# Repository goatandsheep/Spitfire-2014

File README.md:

McMaster Solar Car Club
=======================

Welcome to McMaster University's Solar Car Club's GitHub Repository. This is where we will keep all of our project files. We are currently in the process of transferring files from the Dropbox folder to here.

This is the link to the Solar Car Room Drawer Inventory: http://goo.gl/nMddYb

This is the link to the main Solar Car website: http://www.macsolarcar.com/

If you are new to GitHub, don't fret-we have included a tutorial on how to use it: http://goo.gl/4RcD2u

Note: [.md](https://en.wikipedia.org/wiki/Markdown) files can be opened like .txt files, but look cool up on GitHub

Target Release date: End of February, 2014

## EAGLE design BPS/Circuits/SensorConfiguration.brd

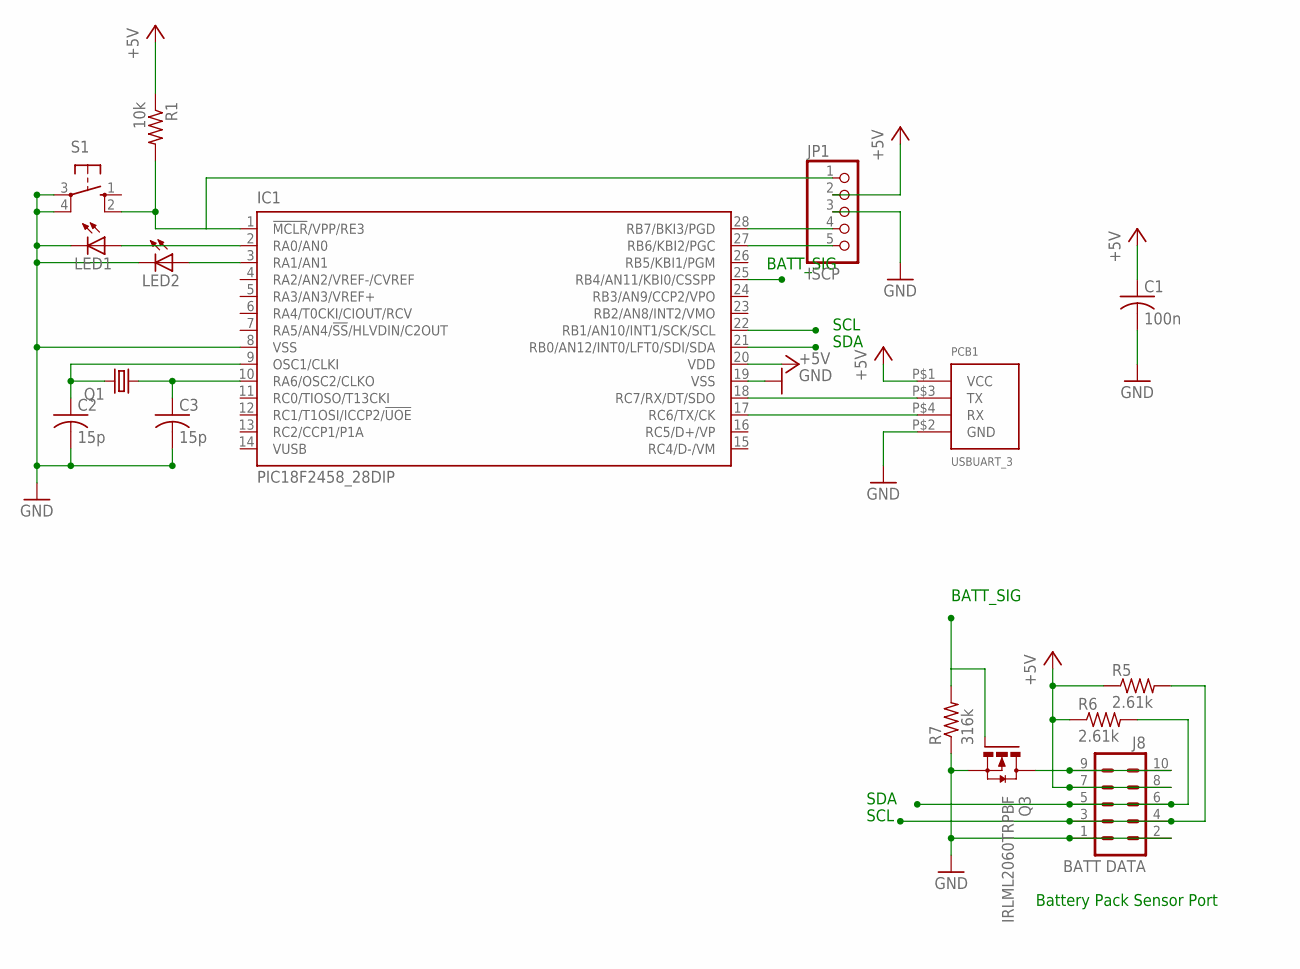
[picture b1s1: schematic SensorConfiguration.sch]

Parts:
C1: 100n; C0805
C2, C3: 15p; C0805
IC1: PIC18F2458_28DIP; DIL28-3
J8: BATT DATA; ML10
JP1: ISCP; 1X05
LED1, LED2: LED5MM
PCB1: USBUART_3; UB232R
Q1: CRYSTALHC49S; HC49/S
Q3: IRLML2060TRPBF; SOT23
R1: 10k; R0805
R5, R6: 2.61k; R0805
R7: 316k; R0805
S1: 10-XX; B3F-10XX

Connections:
+5V: C1.1, IC1.20 (VDD), J8.7, J8.8, JP1.2, PCB1.P$1 (VCC), R1.1, R5.1, R6.1
BSIG: IC1.25 (RB4/AN11/KBI0/CSSPP), Q3.1 (G), R7.2
GND: C1.2, C2.2, C3.2, IC1.8 (VSS), IC1.19 (VSS), J8.1, J8.2, JP1.3, LED1.K (C), LED2.K (C), PCB1.P$2 (GND), Q3.2 (S), R7.1, S1.3, S1.4 (P1)
unnamed: IC1.27 (RB6/KBI2/PGC), JP1.5
unnamed: IC1.18 (RC7/RX/DT/SDO), PCB1.P$3 (TX)
unnamed: IC1.17 (RC6/TX/CK), PCB1.P$4 (RX)
unnamed: IC1.28 (RB7/BKI3/PGD), JP1.4
unnamed: IC1.1 (!MCLR!/VPP/RE3), JP1.1, R1.2, S1.2 (S1)
unnamed: IC1.2 (RA0/AN0), LED1.A
unnamed: J8.9, J8.10, Q3.3 (D)
unnamed: IC1.3 (RA1/AN1), LED2.A
unnamed: C2.1, IC1.9 (OSC1/CLKI), Q1.2
unnamed: C3.1, IC1.10 (RA6/OSC2/CLKO), Q1.1
SCL: IC1.22 (RB1/AN10/INT1/SCK/SCL), J8.3, J8.4, R5.2
SDA: IC1.21 (RB0/AN12/INT0/LFT0/SDI/SDA), J8.5, J8.6, R6.2

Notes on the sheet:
SCL
SDA
Battery Pack Sensor Port
BATT_SIG

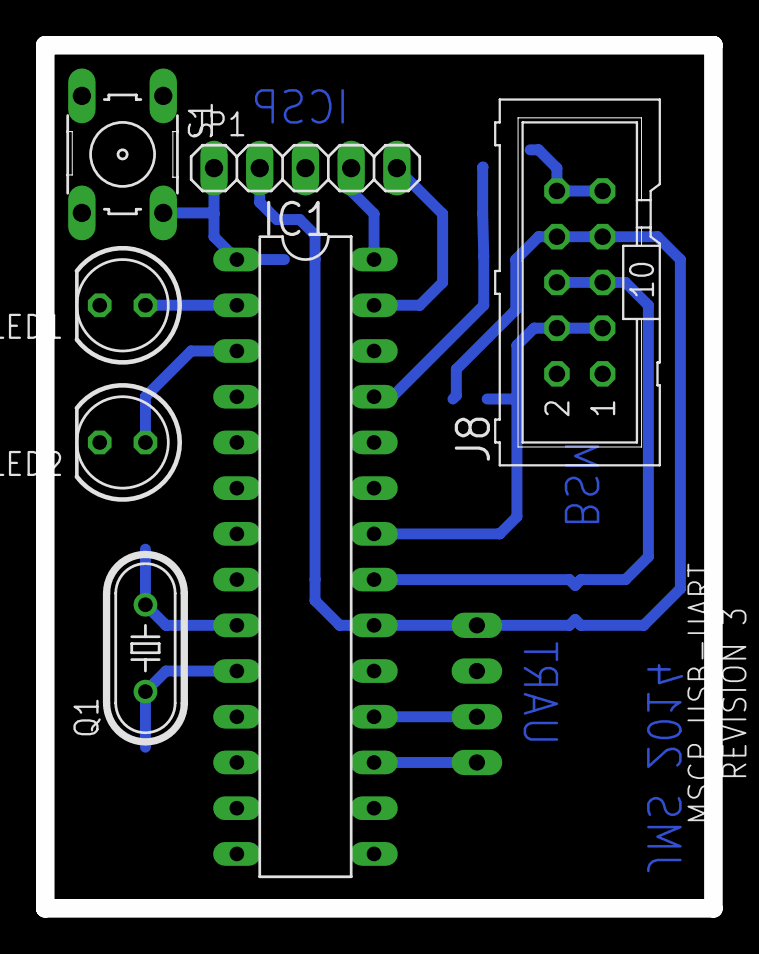
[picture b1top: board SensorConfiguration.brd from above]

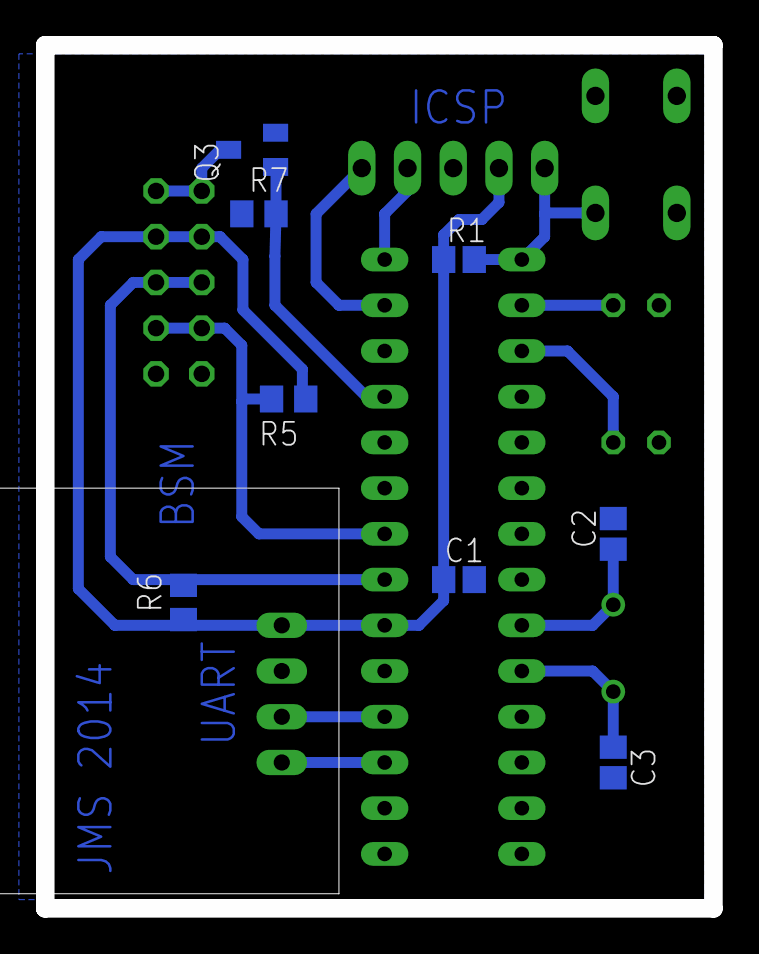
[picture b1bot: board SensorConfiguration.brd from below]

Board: 2 copper layers, 37.1 x 48.0 mm, 16 parts (8 on the bottom side), 15 nets.

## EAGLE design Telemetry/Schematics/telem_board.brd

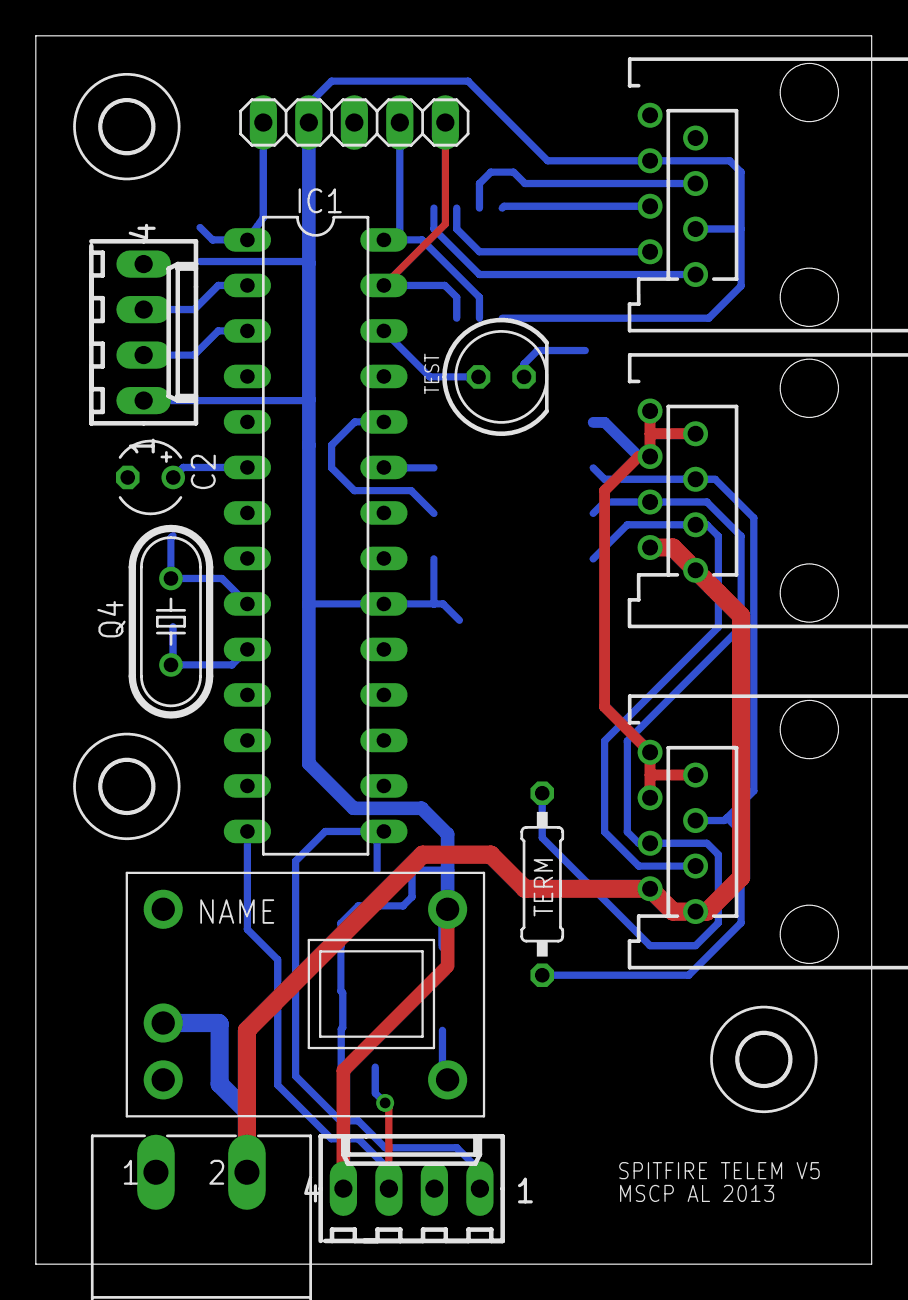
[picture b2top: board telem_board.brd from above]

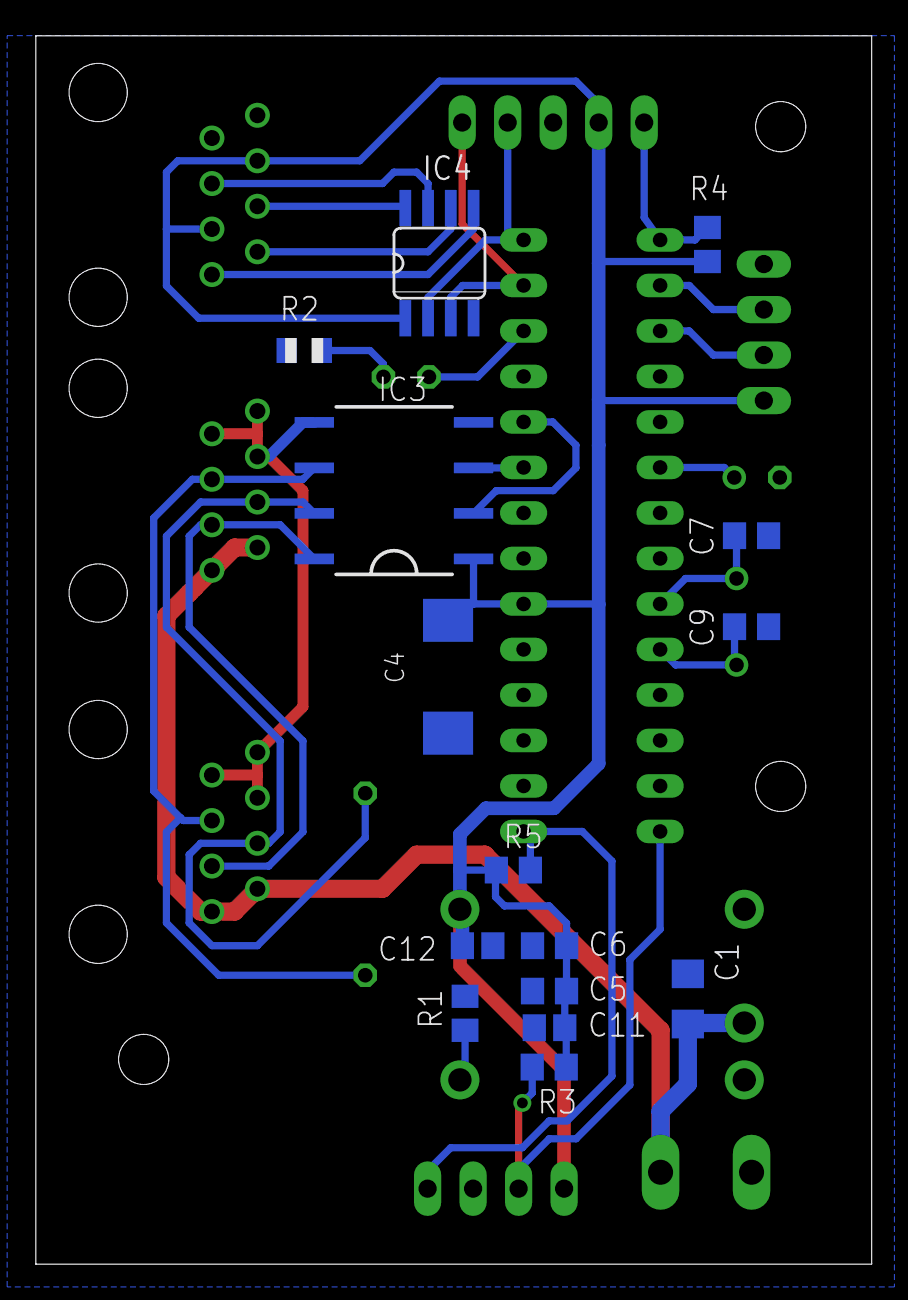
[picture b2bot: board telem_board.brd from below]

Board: 2 copper layers, 46.7 x 68.6 mm, 31 parts (15 on the bottom side), 26 nets.

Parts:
C1: 2.2u; C1206
C2: 10u; TT2D4
C4: 100u; SMC_D
C5: 1u; C0805
C6: 0.1u; C0805
C7, C9: 22p; C0805
C11: 10n; C0805
C12: 4.7u; C0805
H2, H3, H4: MOUNT-HOLE2.8; 2,8
IC1: PIC18F26K80I/SP; DIL28/3
IC2: PTN78000WAH; PTN78000
IC3: ISO1050DUB; DUB-R-PDSO-G8
IC4: SN75LBC179D; SO08
J1: ICD; 1X05
J2, J3: CANBUS; 215877-7
J4: HALLSENS; 6410-04
J5: TEMPSENS; 6410-04
J7: RADIO; 215877-7
Q4: 20M; HC49/S
R1: 21k; R0805
R2, R3, R5: R0805
R4: 10k; R0805
TERM: 100; 0207/10
TEST: LED5MM
X1: +12V; MSTBA2

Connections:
+5V: C4.+, C5.1, C6.2, C11.1, C12.1, IC1.20, IC2.P5, IC3.1, IC4.1, J1.2, J4.1, J5.4, J7.3, J7.6, R3.1, R4.2, R5.1
+12V: C1.1, IC2.P2, J2.1, J2.2, J3.1, J3.2, X1.2
CAN5V: IC3.8, J2.3, J3.3
CANGND: IC3.5, J2.6, J2.7, J2.8, J3.6, J3.7, J3.8
CANH: IC3.7, J2.4, J3.4, TERM.1
CANL: IC3.6, J2.5, J3.5, TERM.2
GND: C1.2, C2.-, C4.-, C5.2, C6.1, C7.2, C9.2, C11.2, C12.2, IC1.8, IC1.19, IC2.P1, IC3.4, IC4.4, J1.3, J4.4, J5.2, J7.7, J7.8, R1.1, R2.1, X1.1
unnamed: IC1.2, J4.3
unnamed: IC1.3, J4.2
unnamed: IC4.7, J7.5
unnamed: IC4.8, J7.4
unnamed: C2.+, IC1.6
unnamed: IC1.23, IC3.3
unnamed: R2.2, TEST.K
unnamed: IC2.P4, R1.2
unnamed: IC1.24, IC3.2
unnamed: IC4.6, J7.2
unnamed: IC1.26, TEST.A
unnamed: IC4.5, J7.1
unnamed: IC1.1, J1.1, R4.1
unnamed: C7.1, IC1.9, Q4.1
unnamed: C9.1, IC1.10, Q4.2
RX: IC1.28, IC4.2, J1.4
SCL: IC1.14, J5.3, R3.2
SDA: IC1.15, J5.1, R5.2
TX: IC1.27, IC4.3, J1.5

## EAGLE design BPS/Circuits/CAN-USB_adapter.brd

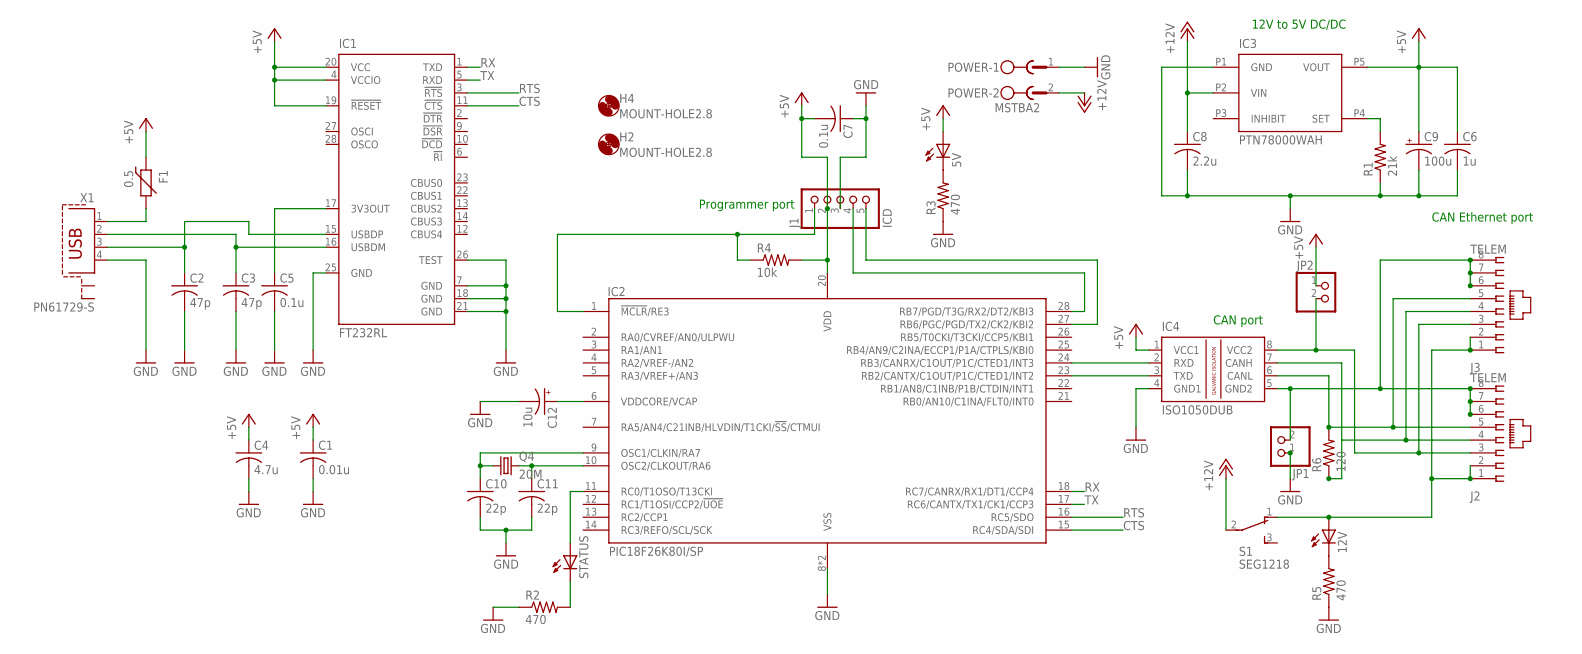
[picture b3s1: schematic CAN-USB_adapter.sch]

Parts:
5V, 12V: LED5MM
C1: 0.01u; C0805
C2, C3: 47p; C0805
C4: 4.7u; C0805
C5, C7: 0.1u; C0805
C6: 1u; C0805
C8: 2.2u; C1206
C9: 100u; SMC_D
C10, C11: 22p; C0805
C12: 10u; TT2D4
F1: 0.5; F1206
H2, H4: MOUNT-HOLE2.8; 2,8
IC1: FT232RL; SSOP28
IC2: PIC18F26K80I/SP; DIL28/3
IC3: PTN78000WAH; PTN78000
IC4: ISO1050DUB; DUB-R-PDSO-G8
J1: ICD; 1X05
J2, J3: TELEM; 215877-7
JP1, JP2: PINHD-1X2; 1X02
POWER: MSTBA2
Q4: 20M; HC49/S
R1: 21k; R0805
R2, R3, R5: 470; R0805
R4: 10k; R0805
R6: 120; 0207/7
S1: SEG1218; EG1218
STATUS: LED5MM
X1: PN61729-S

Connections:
+5V: 5V.A, C1.1, C4.1, C6.1, C7.2, C9.+, F1.1, IC1.4 (VCCIO), IC1.19 (!RESET), IC1.20 (VCC), IC2.20 (VDD), IC3.P5 (VOUT), IC4.1 (VCC1), J1.2, JP2.1, R4.2
+12V: C8.1, IC3.P2 (VIN), POWER.2, S1.2
CTS: IC1.11 (!CTS), IC2.15 (RC4/SDA/SDI)
GND: C1.2, C2.2, C3.2, C4.2, C5.2, C6.2, C7.1, C8.2, C9.-, C10.2, C11.2, C12.-, IC1.7 (GND), IC1.18 (GND), IC1.21 (GND), IC1.25 (GND), IC1.26 (TEST), IC2.8 (VSS), IC2.19 (VSS), IC3.P1 (GND), IC4.4 (GND1), J1.3, JP1.1, POWER.1, R1.1, R2.1, R3.1, R5.1, X1.4
unnamed: C3.1, IC1.16 (USBDM), X1.2
unnamed: C2.1, IC1.15 (USBDP), X1.3
unnamed: C5.1, IC1.17 (3V3OUT)
unnamed: IC2.28 (RB7/PGD/T3G/RX2/DT2/KBI3), J1.4
unnamed: IC2.27 (RB6/PGC/PGD/TX2/CK2/KBI2), J1.5
unnamed: IC2.24 (RB3/CANRX/C1OUT/P1C/CTED1/INT3), IC4.2 (RXD)
unnamed: F1.2, X1.1
unnamed: IC3.P4 (SET), R1.2
unnamed: IC2.23 (RB2/CANTX/C1OUT/P1C/CTED1/INT2), IC4.3 (TXD)
unnamed: R2.2, STATUS.K (C)
unnamed: C10.1, IC2.9 (OSC1/CLKIN/RA7), Q4.1
unnamed: C11.1, IC2.10 (OSC2/CLKOUT/RA6), Q4.2
unnamed: IC2.11 (RC0/T1OSO/T13CKI), STATUS.A
unnamed: C12.+, IC2.6 (VDDCORE/VCAP)
unnamed: 5V.K (C), R3.2
unnamed: 12V.A, J2.1, J2.2, J3.1, J3.2, S1.1 (O)
unnamed: 12V.K (C), R5.2
unnamed: IC4.8 (VCC2), J2.3, J3.3, JP2.2
unnamed: IC2.1 (!MCLR!/RE3), J1.1, R4.1
unnamed: IC4.5 (GND2), J2.6, J2.7, J2.8, J3.6, J3.7, J3.8, JP1.2
unnamed: IC4.7 (CANH), J2.4, J3.4, R6.1
unnamed: IC4.6 (CANL), J2.5, J3.5, R6.2
RTS: IC1.3 (!RTS), IC2.16 (RC5/SDO)
RX: IC1.1 (TXD), IC2.18 (RC7/CANRX/RX1/DT1/CCP4)
TX: IC1.5 (RXD), IC2.17 (RC6/CANTX/TX1/CK1/CCP3)

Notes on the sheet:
12V to 5V DC/DC
Programmer port
CAN port
CAN Ethernet port

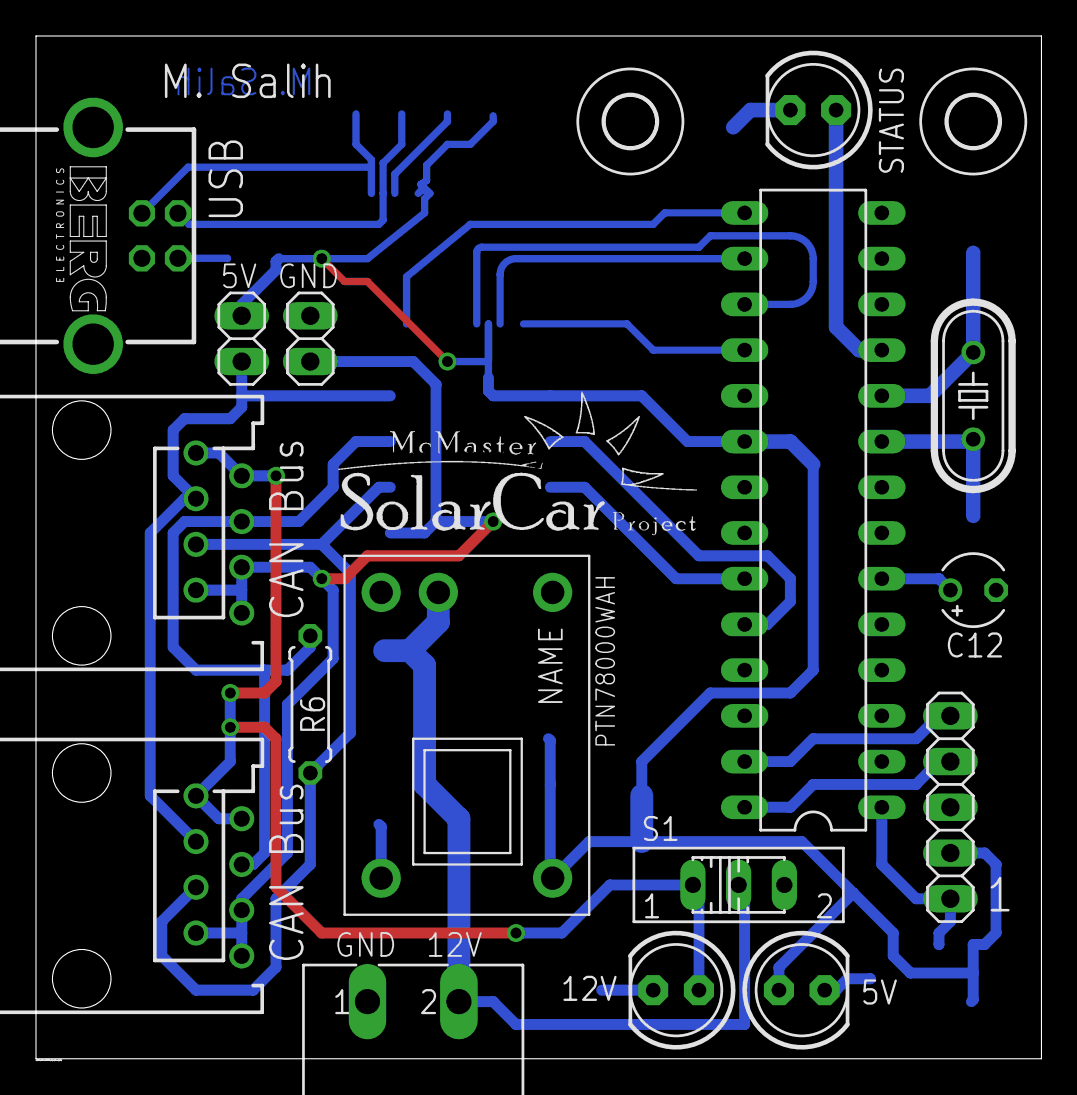
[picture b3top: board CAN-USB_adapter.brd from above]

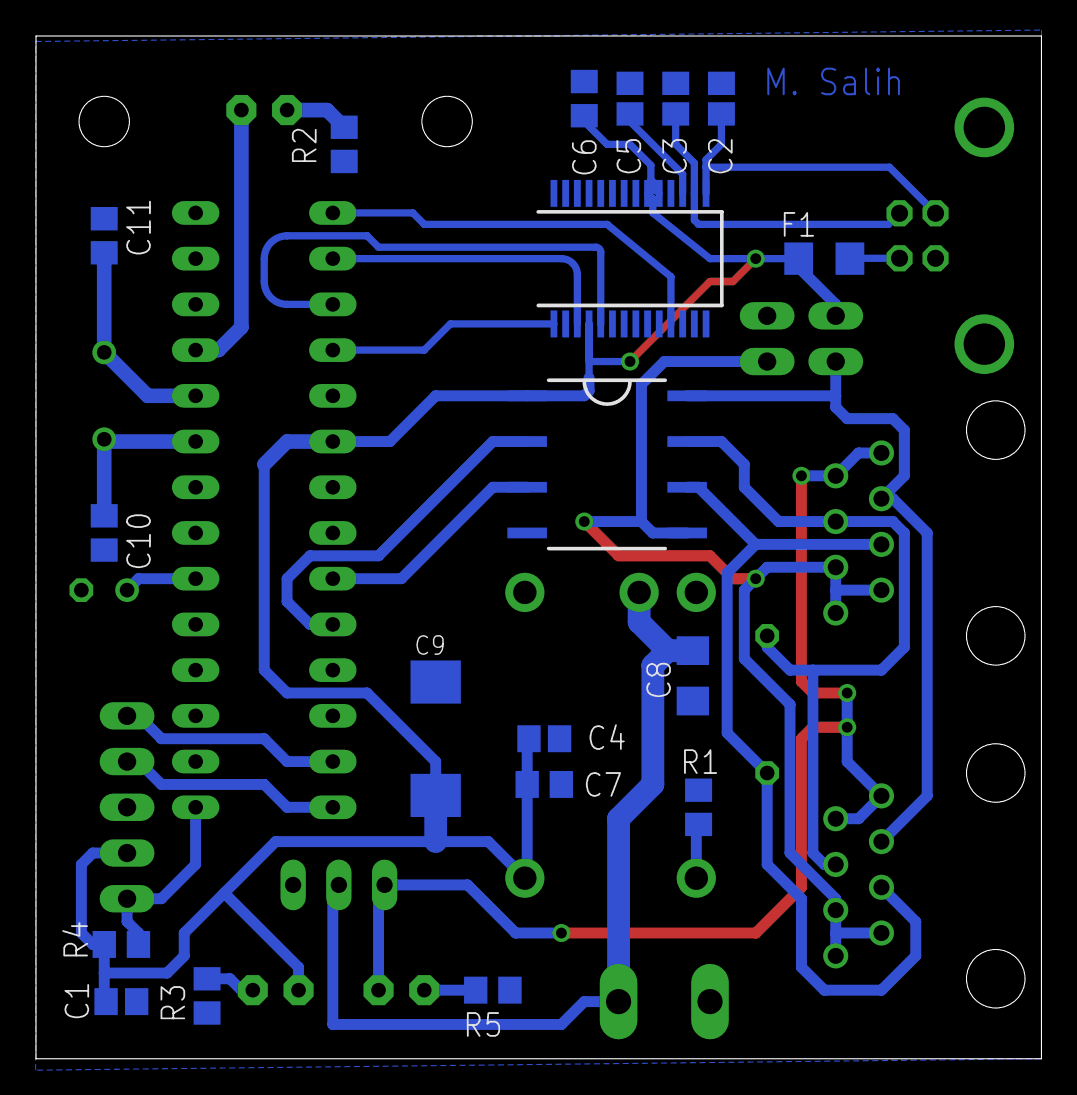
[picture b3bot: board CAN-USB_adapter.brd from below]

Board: 2 copper layers, 55.9 x 56.8 mm, 37 parts (19 on the bottom side), 29 nets.

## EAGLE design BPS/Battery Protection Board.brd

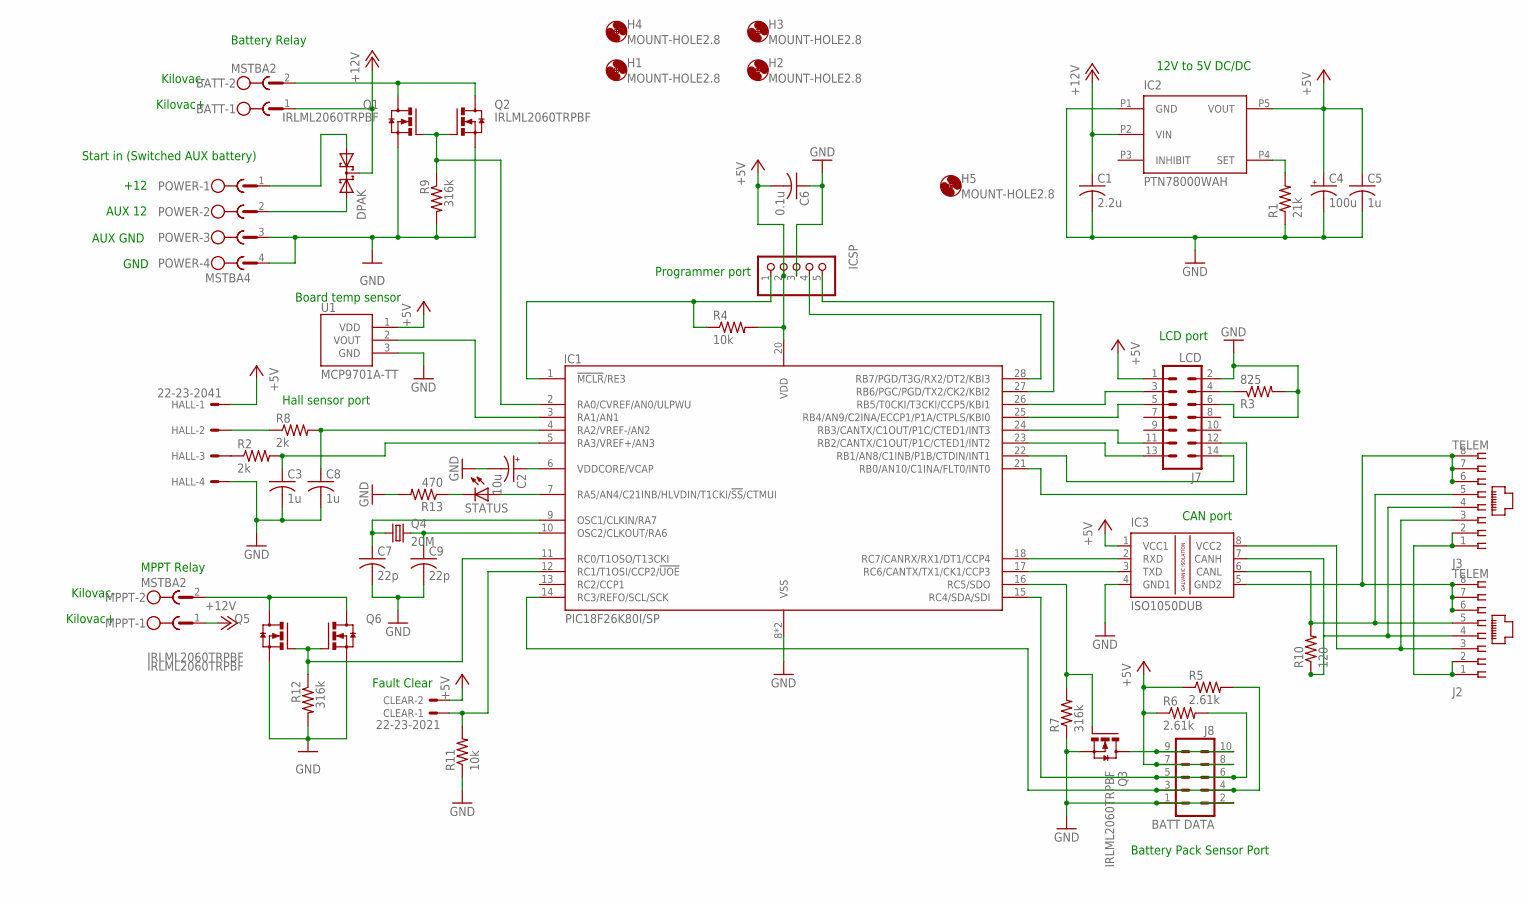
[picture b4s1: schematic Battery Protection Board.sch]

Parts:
BATT: MSTBA2
C1: 2.2u; C1206
C2: 10u; TT2D4
C3, C5, C8: 1u; C0805
C4: 100u; SMC_D
C6: 0.1u; C0805
C7, C9: 22p; C0805
CLEAR: 22-23-2021
DPAK: DIODE_2SCHOTTKY-DPAK; DPAK
H1, H2, H3, H4, H5: MOUNT-HOLE2.8; 2,8
HALL: 22-23-2041
IC1: PIC18F26K80I/SP; DIL28/3
IC2: PTN78000WAH; PTN78000
IC3: ISO1050DUB; DUB-R-PDSO-G8
ICSP: ICD; 1X05
J2, J3: TELEM; 215877-7
J7: LCD; ML14
J8: BATT DATA; ML10
MPPT: MSTBA2
POWER: MSTBA4
Q1, Q2, Q3, Q5, Q6: IRLML2060TRPBF; SOT23
Q4: 20M; HC49/S
R1: 21k; R0805
R2, R8: 2k; R0805
R3: 825; R0805
R4, R11: 10k; R0805
R5, R6: 2.61k; R0805
R7, R9, R12: 316k; R0805
R10: 120; 0207/7
R13: 470; R0805
STATUS: LED5MM
U1: MCP9701A-TT; SOT23

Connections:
+5V: C4.+, C5.1, C6.2, CLEAR.2, HALL.1, IC1.20 (VDD), IC2.P5 (VOUT), IC3.1 (VCC1), ICSP.2, J7.1, J8.7, J8.8, R4.2, R5.1, R6.1, U1.1 (VDD)
+12V: BATT.1, C1.1, DPAK.3 (C), IC2.P2 (VIN), MPPT.1
GND: C1.2, C2.-, C3.2, C4.-, C5.2, C6.1, C7.2, C8.2, C9.2, HALL.4, IC1.8 (VSS), IC1.19 (VSS), IC2.P1 (GND), IC3.4 (GND1), ICSP.3, J7.2, J7.6, J8.1, J8.2, POWER.3, POWER.4, Q1.2 (S), Q2.2 (S), Q3.2 (S), Q5.2 (S), Q6.2 (S), R1.1, R3.2, R7.1, R9.2, R11.1, R12.2, R13.2, U1.3 (GND)
unnamed: IC1.27 (RB6/PGC/PGD/TX2/CK2/KBI2), ICSP.5
unnamed: J7.4, R3.1
unnamed: IC1.15 (RC4/SDA/SDI), J8.5, J8.6, R6.2
unnamed: IC1.16 (RC5/SDO), Q3.1 (G), R7.2
unnamed: C2.+, IC1.6 (VDDCORE/VCAP)
unnamed: IC1.3 (RA1/AN1), U1.2 (VOUT)
unnamed: J8.9, J8.10, Q3.3 (D)
unnamed: IC2.P4 (SET), R1.2
unnamed: IC1.7 (RA5/AN4/C21INB/HLVDIN/T1CKI/!SS!/CTMUI), STATUS.A
unnamed: IC1.14 (RC3/REFO/SCL/SCK), J8.3, J8.4, R5.2
unnamed: IC1.17 (RC6/CANTX/TX1/CK1/CCP3), IC3.3 (TXD)
unnamed: DPAK.2 (A2), POWER.2
unnamed: DPAK.1 (A1), POWER.1
unnamed: IC3.7 (CANH), J2.4, J3.4, R10.1
unnamed: IC3.8 (VCC2), J2.3, J3.3
unnamed: J2.1, J2.2, J3.1, J3.2
unnamed: IC1.22 (RB1/AN8/C1INB/P1B/CTDIN/INT1), J7.14
unnamed: IC1.18 (RC7/CANRX/RX1/DT1/CCP4), IC3.2 (RXD)
unnamed: IC1.21 (RB0/AN10/C1INA/FLT0/INT0), J7.12
unnamed: IC1.1 (!MCLR!/RE3), ICSP.1, R4.1
unnamed: IC1.28 (RB7/PGD/T3G/RX2/DT2/KBI3), ICSP.4
unnamed: IC1.23 (RB2/CANTX/C1OUT/P1C/CTED1/INT2), J7.13
unnamed: IC1.24 (RB3/CANTX/C1OUT/P1C/CTED1/INT3), J7.11
unnamed: C7.1, IC1.9 (OSC1/CLKIN/RA7), Q4.1
unnamed: C9.1, IC1.10 (OSC2/CLKOUT/RA6), Q4.2
unnamed: IC1.25 (RB4/AN9/C2INA/ECCP1/P1A/CTPLS/KBI0), J7.5
unnamed: C8.1, IC1.4 (RA2/VREF-/AN2), R8.2
unnamed: IC1.26 (RB5/T0CKI/T3CKI/CCP5/KBI1), J7.3
unnamed: IC1.2 (RA0/CVREF/AN0/ULPWU), Q1.1 (G), Q2.1 (G), R9.1
unnamed: R13.1, STATUS.K (C)
unnamed: C3.1, IC1.5 (RA3/VREF+/AN3), R2.2
unnamed: IC3.5 (GND2), J2.6, J2.7, J2.8, J3.6, J3.7, J3.8
unnamed: HALL.3, R2.1
unnamed: IC1.11 (RC0/T1OSO/T13CKI), Q5.1 (G), Q6.1 (G), R12.1
unnamed: HALL.2, R8.1
unnamed: BATT.2, Q1.3 (D), Q2.3 (D)
unnamed: MPPT.2, Q5.3 (D), Q6.3 (D)
unnamed: CLEAR.1, IC1.12 (RC1/T1OSI/CCP2/!UOE!), R11.2
unnamed: IC3.6 (CANL), J2.5, J3.5, R10.2

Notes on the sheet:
Start in (Switched AUX battery)
+12
Kilovac+
Kilovac-
LCD port
12V to 5V DC/DC
Programmer port
CAN port
Board temp sensor
Hall sensor port
Battery Relay
MPPT Relay
Fault Clear
GND
AUX 12
AUX GND
Battery Pack Sensor Port

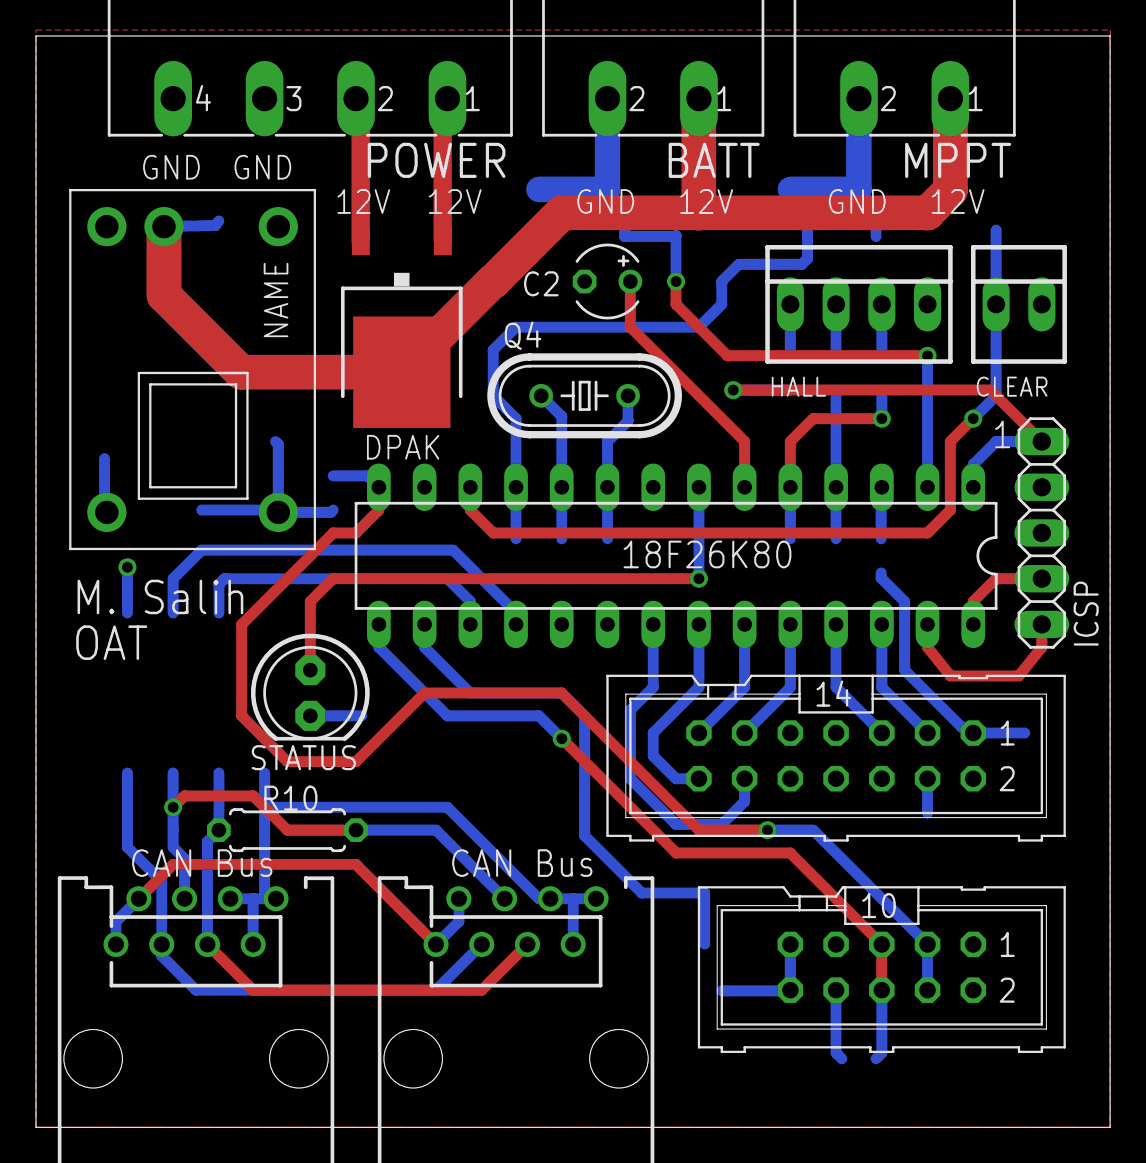
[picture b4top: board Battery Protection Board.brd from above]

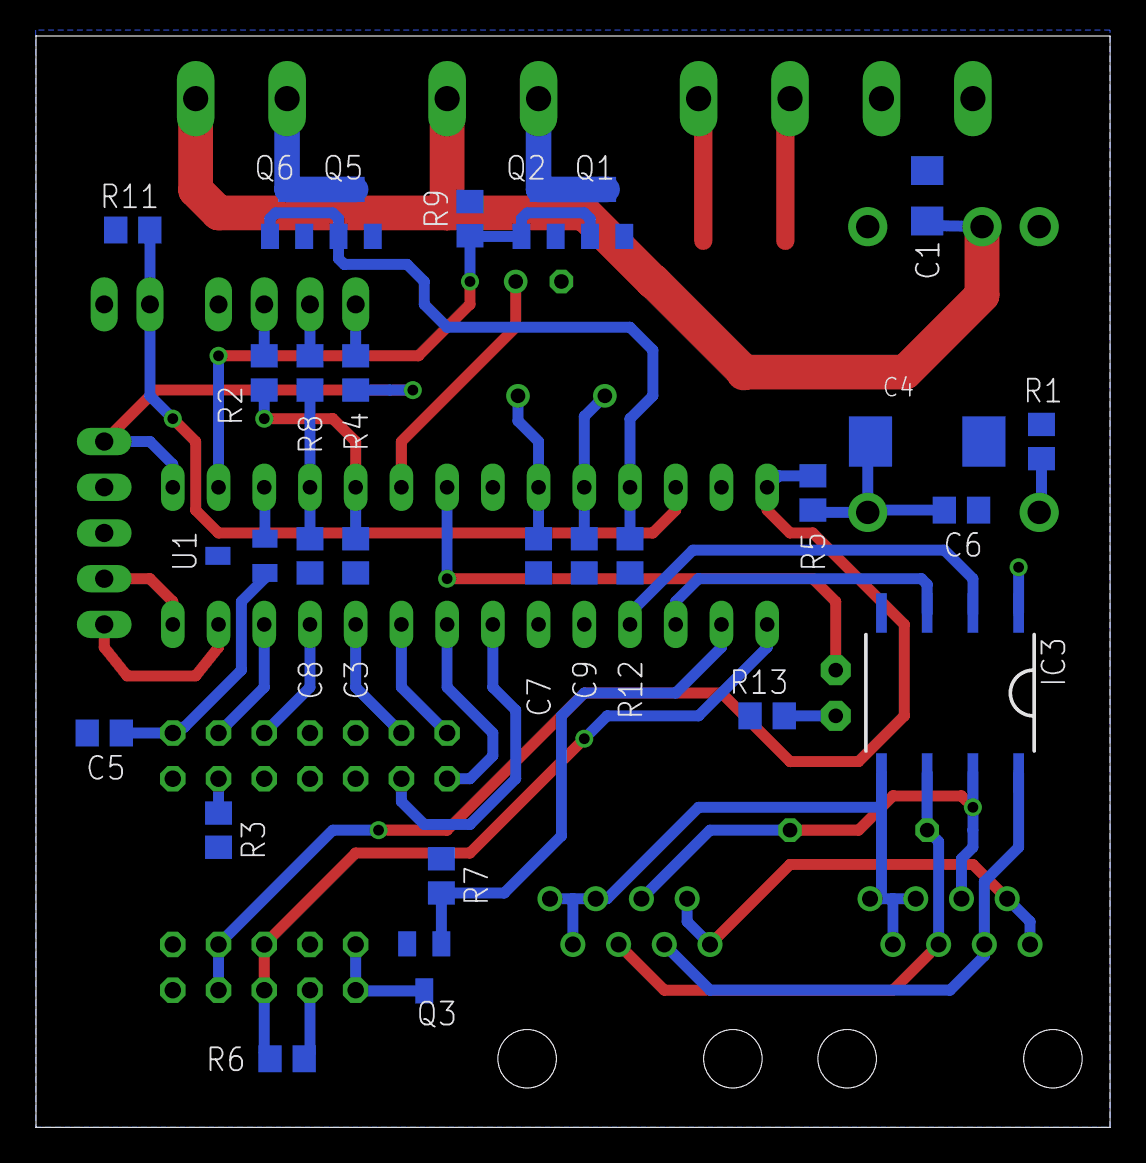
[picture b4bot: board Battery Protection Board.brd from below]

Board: 2 copper layers, 59.7 x 60.6 mm, 49 parts (27 on the bottom side), 42 nets.

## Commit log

2013-11-21 Day 1
    Just looking at I^2 C for the first time
2013-11-21 Test Commit
    First official GitHub commit that's an update of anything, so just
    testing to see if it works
2013-11-21 add_reqs
2013-11-21 Changed EVERYTHING
    Hated previous project so restarted
2013-11-21 Update README.md
    Added the link to the Inventory Document
2013-11-21 Added .gitignore
2013-11-26 add in ds2764 spec sheet
2013-11-26 Changed pretty much nothing, but added the manual
    LED is turning on and off, but any changes are stopping the LED and
    nothing is coming from the serial port output
2013-11-26 Changed printc to printf
2013-11-26 added second address
2013-11-26 Closing Commit for the Semester
    Still results in wrong output
2014-01-10 Previous problems fixed
    Lun (who is refusing to use git) fixed the file!
2014-01-16 ALL NEW ALL FREE INFO ON HALL EFFECT SENSORS
2014-01-17 Added hall effect board calibration
2014-01-18 Added calibration data
    Added in libreoffice format so its crossplatform
2014-01-18 updated .gitignore
2014-01-20 Github sucks
2014-01-21 Add calibration docs
2014-01-21 Added CANbus library header
    because lun forgot it
2014-01-24 Clean Up CAN_Nodes
2014-01-25 Renamed CAN example files and cleaned up the CAN library
    The changes made to the CAN library were just consistency changes in
    the commenting style, the only functionality change was commenting out
    the call to can_set_functional_mode() that was found to hang the
    program on can_init() calls
2014-01-27 Added Readme
2014-01-27 Real initial commit
2014-01-27 Updated readme
    added stuff
2014-01-30 Add more things/Orginization
2014-01-31 CANBus send/receive now working
2014-01-31 type
2014-01-31 Paul told me "Nightly commit"
2014-02-02 fixed { style
2014-02-02 Fixed an #end macro to an #endif macro
    THIS FUCKING LITTLE TYPE TOOK ME 2 FUCKING HOURS TO FIND AND FIX
    GODDAMNIT
2014-02-03 added project file
2014-02-06 readme
    added solar car website to readme for employees to see
2014-02-07 fixed paul's broken code
2014-02-11 Finally fixed the for loop error
    The problem was we were indexing rawVoltageData with an 8bit int instead
    of a 16bit int, this was causing casting problems since rawVoltageData
    is an array of uint16.
    Also fixed formatting in other files and removed commented out line in
    can_init()
2014-02-19 Mostly changed orginization
2014-02-19 packet now indexes from 0 instead of 1
2014-02-19 12:31 19/02/2014
2014-02-21 2121:31 20/02/2014
2014-02-21 from dropbox
2014-02-21 Starting basic protection logic
2014-02-21 Changed flex_lcd formatting
2014-02-26 More sensor monitoring code.
    Sensor data is now stored in a struct with the sensor ID, temp and
    voltage reading, as well as the temperature and voltage error counters
2014-02-27 Started to give functions a header comment
2014-03-04 22:17 03/03/2014
    Paul made me commit
2014-03-05 cosmetic changes, added relay text code, fixed code in setPacketFunction
2014-03-06 Readme update
    Added link to GitHub tutorial to Readm
2014-03-06 Updated readme
    why do we have 2 repos :(
    oh well, I'll have this here, for now...
2014-03-06 Added LCD Module Files
2014-03-06 Nuff Said
2014-03-06 More documentation
2014-03-06 i trusted u paul
2014-03-06 Updated readme
    Added link to new repo
2014-03-11 21:38 10/03/2014
    Added theory LCD code to BPS.c
    Created BPSProtocolReceiveExampleCode
2014-03-17 Organization + Documentation
2014-03-17 Merge branch 'master' of https://github.com/goatandsheep/MacEngSolarBatteryProtection2014
    Conflicts:
    flex_lcd_PROT6.c
2014-03-17 Renamed library
    I like this better
2014-03-18 Added circuitry
2014-03-18 Added stuff
2014-03-18 telem_boardV2
2014-03-18 telem_board_v3
2014-03-18 telem_board_v4
2014-03-18 telem_board_v6
2014-03-18 real telem_board_v6
    previous one was v5
2014-03-18 telem_board
2014-03-18 Renamed the Schematics folder
    its almost 9
2014-03-18 Set up folders for merge
2014-03-18 Paul told me
2014-03-20 Removed redundant circuitry folder in telem
2014-03-20 "Added driver display code"
    -Quote by Paul Correira
2014-03-20 Removed them
2014-03-20 Added them again
2014-03-20 Started updating driver display
2014-03-20 Removed schematics from code file
2014-03-20 added BPS select info function
2014-03-20 Added BPS function and BPS receive in main
2014-03-20 More display functions
2014-03-24 Driver display documentation/organization
2014-03-26 Started telemetry code
2014-03-26 Changed BPS Protocol
    Documentation only though, Lun changed the code. Also added the
    temperature sensor data sheet
2014-03-27 Added telemetry MOTOR CONT and BPS receive code
2014-03-27 Added eagle files for sensor configuration
    Code soon
2014-03-27 Modified BPS documentation
2014-03-27 Added sensor config code
2014-03-27 Changed things
2014-03-28 Created new Driver display code file
2014-03-28 plug this mouse in
2014-03-28 Docs
2014-03-28 Deleted old driver display
2014-03-28 ddisp and telem
2014-03-28 Moved CAN and LCD libraries to shared folder
    Added docs for the issues with floating point numbers
2014-03-29 Fixed memcpy syntax, added float utils
    memcpy syntax should be (DST, SRC, N), not src, dst.
2014-04-01 commit and synch
2014-04-01 driver display docs
2014-04-15 Add Driver Control stuff
2014-04-23 Added to do list
2014-04-23 Added LED datasheets
2014-04-23 Driver display changes
2014-04-27 Gitignore temp files
    just added some stuff to the gitignore
2014-05-02 added things
2014-05-02 Revert "added things"
    This reverts commit 3bedffcbdf7fcd56a5a3bfa4455c198752032db1.
2014-05-02 added devices 18f26k80.h
2014-05-02 Added LCD DataSheet
2014-05-02 Allow lcd library to use different pins
2014-05-06 Added Components Library
    used to be named eagle-6.2.0/lbr/MSCP_2011_v2.lbr
    I also added a component for a 2x1 led.
    It is also on Dropbox, but I'm trying to use GitHub more, since it is
    simpler
2014-05-06 Changed driver display
2014-05-06 Added quotes
2014-05-06 Added info about markdown language to readme
2014-05-06 playing with markup
